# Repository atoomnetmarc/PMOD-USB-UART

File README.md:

This converts USB to UART on a PMOD connector.

*Status*: working.

My [Kicad library](https://github.com/atoomnetmarc/ATOOMNETKICAD) is used in this project.

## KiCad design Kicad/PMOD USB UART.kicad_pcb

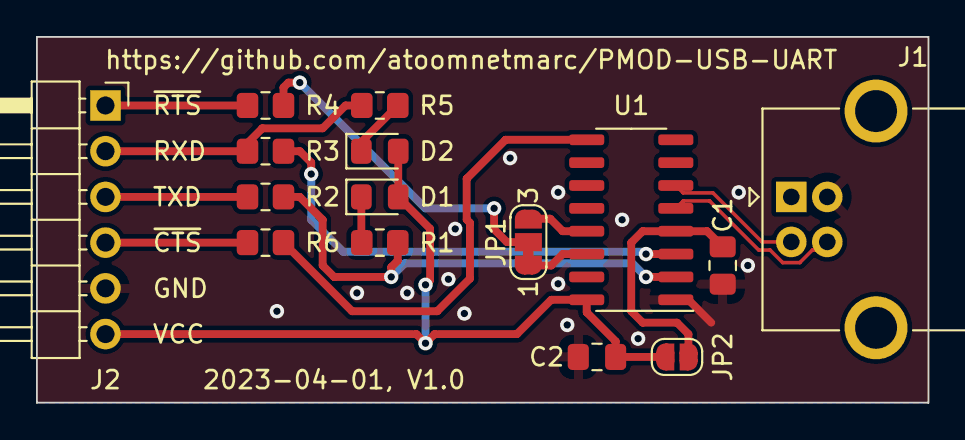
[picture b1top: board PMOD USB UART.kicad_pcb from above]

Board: 2 copper layers, 49.5 x 20.3 mm, 15 parts (0 on the bottom side), 17 nets.

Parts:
C1, C2: 100n; C_0805_2012Metric_Pad1.18x1.45mm_HandSolder
D1, D2: Blue; LED_0805_2012Metric_Pad1.15x1.40mm_HandSolder
J1: USB_B; USB_B_OST_USB-B1HSxx_Horizontal
J2: Pmod peripheral UART; PinHeader_1x06_P2.54mm_Horizontal
JP1: SolderJumper_3_Bridged12; SolderJumper-3_P1.3mm_Bridged12_RoundedPad1.0x1.5mm_NumberL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
JP2: Open: 5V, Closed:3V3; SolderJumper-2_P1.3mm_Open_RoundedPad1.0x1.5mm
R1, R5: 1k; R_0805_2012Metric_Pad1.20x1.40mm_HandSolder
R2, R3, R4, R6: 100R; R_0805_2012Metric_Pad1.20x1.40mm_HandSolder
U1: CH340C; SOIC-16_3.9x9.9mm_P1.27mm

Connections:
+3V3: C1.1, JP2.1 (A), U1.4 (V3)
/RXD: R3.1, U1.3 (RXD)
/TXD: R1.2, R2.1, U1.2 (TXD)
/USB+: J1.3 (D+), U1.5 (UD+)
/USB-: J1.2 (D-), U1.6 (UD-)
/~CTS: R6.1, U1.9 (~CTS)
/~DTR: JP1.3 (B), U1.13 (~DTR)
/~RTS: JP1.1 (A), U1.14 (~RTS)
GND: C1.2, C2.2, J1.4 (GND), J2.5 (GND), U1.1 (GND)
unnamed: D1.1 (K), R1.1
unnamed: D2.1 (K), R5.1
unnamed: JP1.2 (C), R4.1
USB_RXD: J2.2 (TXD), R3.2, R5.2
USB_TXD: J2.3 (RXD), R2.2
USB_~CTS: J2.4 (~RTS/IO), R6.2
USB_~RTS: J2.1 (~CTS/IO), R4.2
VCC: C2.1, D1.2 (A), D2.2 (A), J2.6 (VCC), JP2.2 (B), U1.16 (VCC)

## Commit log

2023-03-31 First version.
2023-03-31 Ignore zip
2023-04-01 Small tweaks.
2023-05-02 Soldered.
2024-09-27 It works!
2026-01-23 Add CONTRIBUTING.md

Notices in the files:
Kicad/PMOD USB UART.kicad_pcb:
Apache License, version 2.0
README.md:
License: Apache 2.0
